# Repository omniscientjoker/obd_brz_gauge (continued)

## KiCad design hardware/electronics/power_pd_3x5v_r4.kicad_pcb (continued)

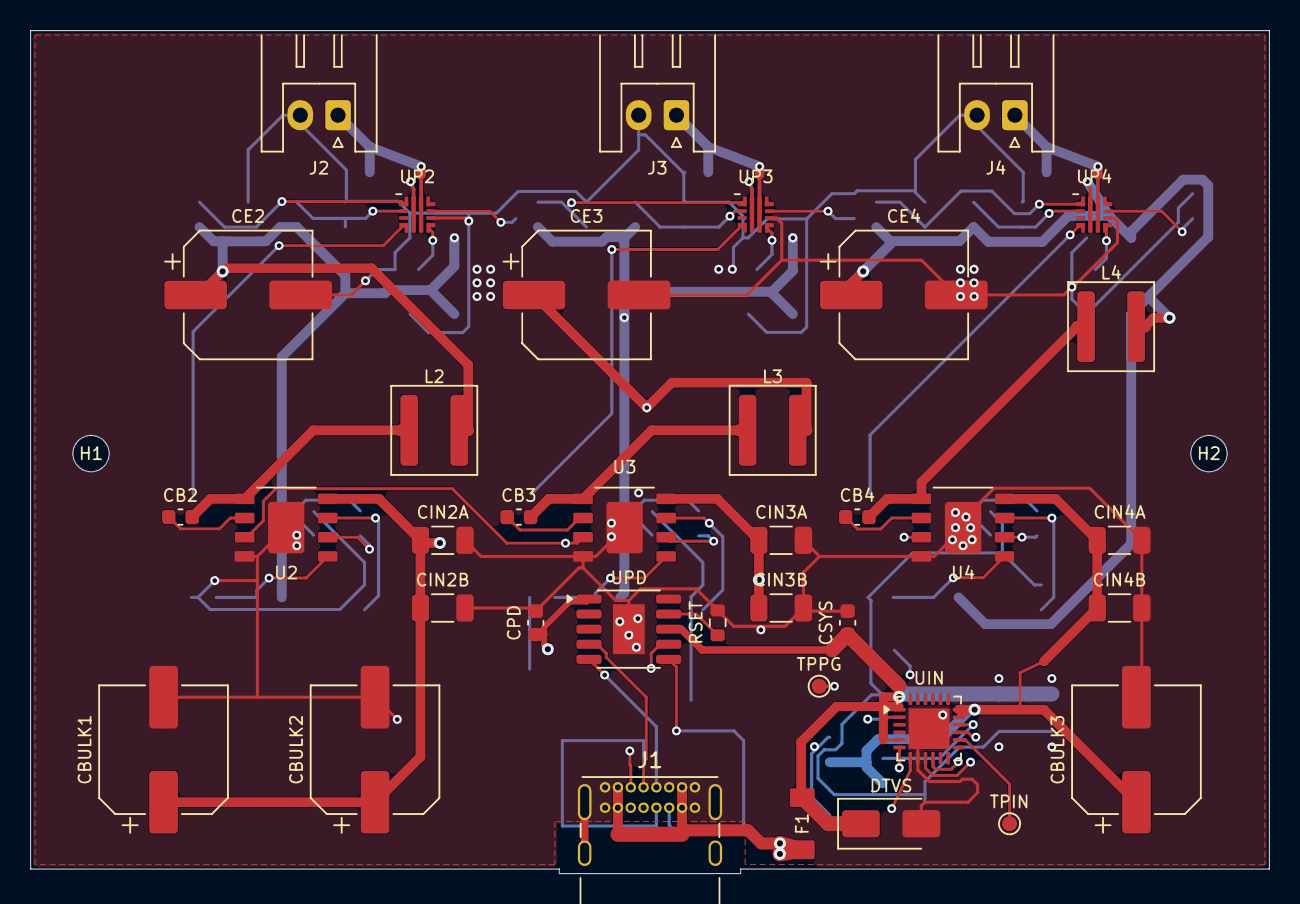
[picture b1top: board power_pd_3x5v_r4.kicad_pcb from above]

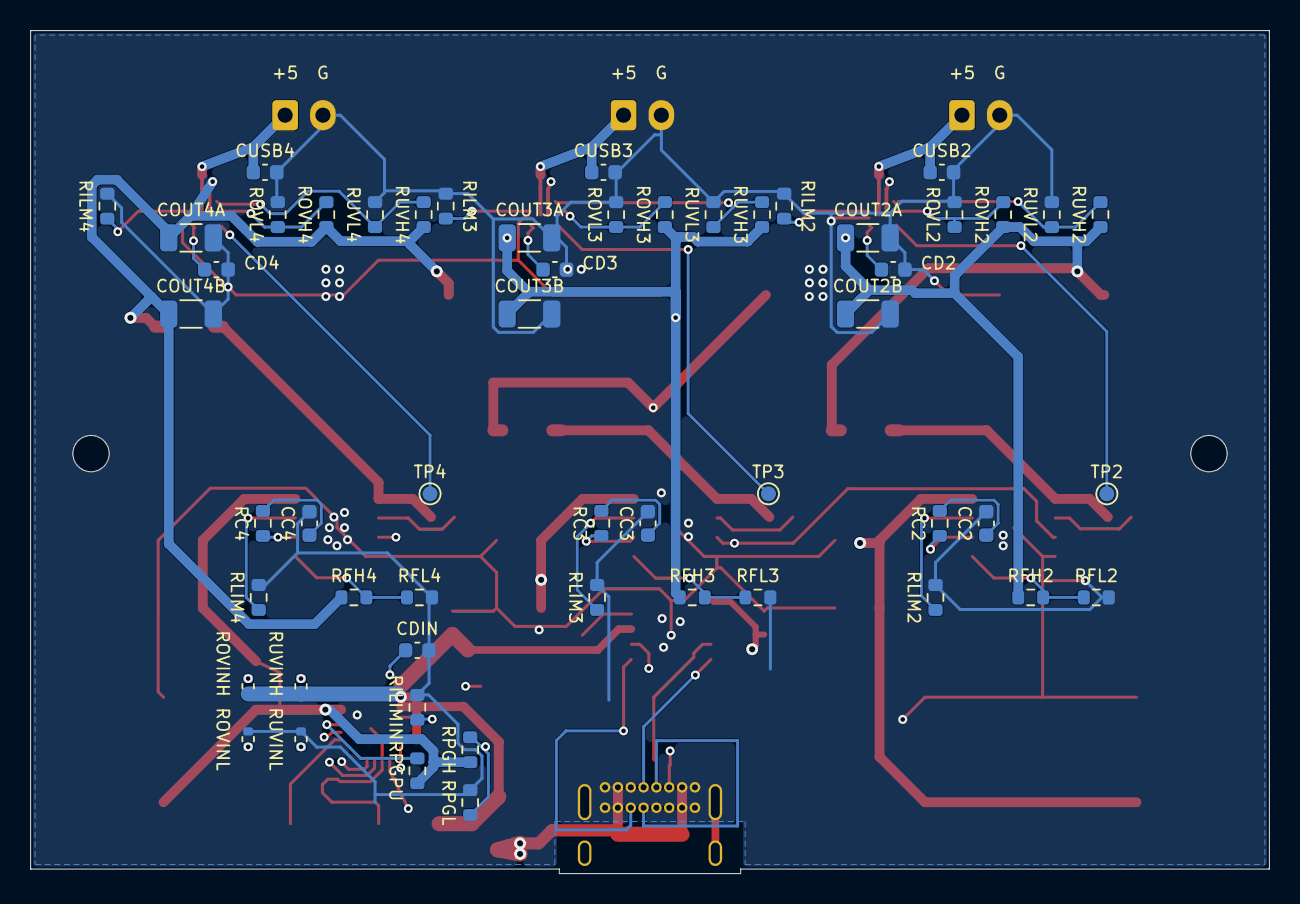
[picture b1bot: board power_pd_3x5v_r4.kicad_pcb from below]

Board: 4 copper layers, 82.0 x 55.8 mm, 93 parts (54 on the bottom side), 55 nets.

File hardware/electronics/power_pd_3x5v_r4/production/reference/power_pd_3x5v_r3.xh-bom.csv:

"Refs","Value","Footprint","Qty","DNP"
"CB2","100nF 50V","Capacitor_SMD:C_0603_1608Metric","1",""
"CB3","100nF 50V","Capacitor_SMD:C_0603_1608Metric","1",""
"CB4","100nF 50V","Capacitor_SMD:C_0603_1608Metric","1",""
"CBULK1","82uF 35V POLYMER","Capacitor_SMD:CP_Elec_8x6.9","1",""
"CBULK2","82uF 35V POLYMER","Capacitor_SMD:CP_Elec_8x6.9","1",""
"CBULK3","82uF 35V POLYMER","Capacitor_SMD:CP_Elec_8x6.9","1",""
"CC2","2.7nF C0G 50V","Capacitor_SMD:C_0603_1608Metric","1",""
"CC3","2.7nF C0G 50V","Capacitor_SMD:C_0603_1608Metric","1",""
"CC4","2.7nF C0G 50V","Capacitor_SMD:C_0603_1608Metric","1",""
"CD2","8.2nF C0G 50V","Capacitor_SMD:C_0603_1608Metric","1",""
"CD3","8.2nF C0G 50V","Capacitor_SMD:C_0603_1608Metric","1",""
"CD4","8.2nF C0G 50V","Capacitor_SMD:C_0603_1608Metric","1",""
"CDIN?","100nF 50V","Capacitor_SMD:C_0603_1608Metric","1",""
"CE2","100uF 25V POLYMER","Capacitor_SMD:CP_Elec_8x6.9","1",""
"CE3","100uF 25V POLYMER","Capacitor_SMD:CP_Elec_8x6.9","1",""
"CE4","100uF 25V POLYMER","Capacitor_SMD:CP_Elec_8x6.9","1",""
"CIN2A?","10uF 50V X5R","Capacitor_SMD:C_1206_3216Metric","1",""
"CIN2B?","10uF 50V X5R","Capacitor_SMD:C_1206_3216Metric","1",""
"CIN3A?","10uF 50V X5R","Capacitor_SMD:C_1206_3216Metric","1",""
"CIN3B?","10uF 50V X5R","Capacitor_SMD:C_1206_3216Metric","1",""
"CIN4A?","10uF 50V X5R","Capacitor_SMD:C_1206_3216Metric","1",""
"CIN4B?","10uF 50V X5R","Capacitor_SMD:C_1206_3216Metric","1",""
"COUT2A?","22uF 25V X5R","Capacitor_SMD:C_1206_3216Metric","1",""
"COUT2B?","22uF 25V X5R","Capacitor_SMD:C_1206_3216Metric","1",""
"COUT3A?","22uF 25V X5R","Capacitor_SMD:C_1206_3216Metric","1",""
"COUT3B?","22uF 25V X5R","Capacitor_SMD:C_1206_3216Metric","1",""
"COUT4A?","22uF 25V X5R","Capacitor_SMD:C_1206_3216Metric","1",""
"COUT4B?","22uF 25V X5R","Capacitor_SMD:C_1206_3216Metric","1",""
"CPD?","1uF 50V X5R","Capacitor_SMD:C_0603_1608Metric","1",""
"CSYS?","1uF 50V X5R","Capacitor_SMD:C_0603_1608Metric","1",""
"CUSB2","1uF 50V X5R","Capacitor_SMD:C_0603_1608Metric","1",""
"CUSB3","1uF 50V X5R","Capacitor_SMD:C_0603_1608Metric","1",""
"CUSB4","1uF 50V X5R","Capacitor_SMD:C_0603_1608Metric","1",""
"DTVS?","SMAJ16A","Diode_SMD:D_SMA","1",""
"F1","3A 63VDC FAST","GaugePower:SF_1206F_Recommended","1",""
"J1","USB-C PD 15V/3A","Connector_USB:USB_C_Receptacle_GCT_USB4085","1",""
"J2","XH2.50-2P 5V OUTPUT","GaugePower:JST_XH_S2B-XH-A_1x02_P2.50mm_Horizontal_Assembly","1",""
"J3","XH2.50-2P 5V OUTPUT","GaugePower:JST_XH_S2B-XH-A_1x02_P2.50mm_Horizontal_Assembly","1",""
"J4","XH2.50-2P 5V OUTPUT","GaugePower:JST_XH_S2B-XH-A_1x02_P2.50mm_Horizontal_Assembly","1",""
"L2","6.8uH / 6A Isat","Inductor_SMD:L_Coilcraft_XAL5050-XXX","1",""
"L3","6.8uH / 6A Isat","Inductor_SMD:L_Coilcraft_XAL5050-XXX","1",""
"L4","6.8uH / 6A Isat","Inductor_SMD:L_Coilcraft_XAL5050-XXX","1",""
"RC2","24k","Resistor_SMD:R_0603_1608Metric","1",""
"RC3","24k","Resistor_SMD:R_0603_1608Metric","1",""
"RC4","24k","Resistor_SMD:R_0603_1608Metric","1",""
"RFH2","52.3k 0.1%","Resistor_SMD:R_0603_1608Metric","1",""
"RFH3","52.3k 0.1%","Resistor_SMD:R_0603_1608Metric","1",""
"RFH4","52.3k 0.1%","Resistor_SMD:R_0603_1608Metric","1",""
"RFL2","10k 0.1%","Resistor_SMD:R_0603_1608Metric","1",""
"RFL3","10k 0.1%","Resistor_SMD:R_0603_1608Metric","1",""
"RFL4","10k 0.1%","Resistor_SMD:R_0603_1608Metric","1",""
"RILIMIN?","8.25k 1%","Resistor_SMD:R_0603_1608Metric","1",""
"RILM2","1.65k 1%","Resistor_SMD:R_0603_1608Metric","1",""
"RILM3","1.65k 1%","Resistor_SMD:R_0603_1608Metric","1",""
"RILM4","1.65k 1%","Resistor_SMD:R_0603_1608Metric","1",""
"RLIM2","84.5k 1%","Resistor_SMD:R_0603_1608Metric","1",""
"RLIM3","84.5k 1%","Resistor_SMD:R_0603_1608Metric","1",""
"RLIM4","84.5k 1%","Resistor_SMD:R_0603_1608Metric","1",""
"ROVH2","34k 0.1%","Resistor_SMD:R_0603_1608Metric","1",""
"ROVH3","34k 0.1%","Resistor_SMD:R_0603_1608Metric","1",""
"ROVH4","34k 0.1%","Resistor_SMD:R_0603_1608Metric","1",""
"ROVINH?","133k 0.1%","Resistor_SMD:R_0402_1005Metric","1",""
"ROVINL?","10k 0.1%","Resistor_SMD:R_0402_1005Metric","1",""
"ROVL2","10k 0.1%","Resistor_SMD:R_0603_1608Metric","1",""
"ROVL3","10k 0.1%","Resistor_SMD:R_0603_1608Metric","1",""
"ROVL4","10k 0.1%","Resistor_SMD:R_0603_1608Metric","1",""
"RPGH?","100k 0.1%","Resistor_SMD:R_0603_1608Metric","1",""
"RPGL?","10k 0.1%","Resistor_SMD:R_0603_1608Metric","1",""
"RPGPU?","100k","Resistor_SMD:R_0603_1608Metric","1",""
"RSET?","56k 1%","Resistor_SMD:R_0603_1608Metric","1",""
"RUVH2","28k 0.1%","Resistor_SMD:R_0603_1608Metric","1",""
"RUVH3","28k 0.1%","Resistor_SMD:R_0603_1608Metric","1",""
"RUVH4","28k 0.1%","Resistor_SMD:R_0603_1608Metric","1",""
"RUVINH?","100k 0.1%","Resistor_SMD:R_0402_1005Metric","1",""
"RUVINL?","10k 0.1%","Resistor_SMD:R_0402_1005Metric","1",""
"RUVL2","10k 0.1%","Resistor_SMD:R_0603_1608Metric","1",""
"RUVL3","10k 0.1%","Resistor_SMD:R_0603_1608Metric","1",""
"RUVL4","10k 0.1%","Resistor_SMD:R_0603_1608Metric","1",""
"U2","RT7272BGSP","GaugePower:RT7272BGSP_PSOP8_Option2","1",""
"U3","RT7272BGSP","GaugePower:RT7272BGSP_PSOP8_Option2","1",""
"U4","RT7272BGSP","GaugePower:RT7272BGSP_PSOP8_Option2","1",""
"UIN?","TPS26630RGER","GaugePower:Texas_RGE0024H_VQFN-24-1EP_4x4mm_P0.5mm_EP2.7x2.7mm_Assembly","1",""
"UP2","TPS259470LRPWR","GaugePower:TI_RPW0010A","1",""
"UP3","TPS259470LRPWR","GaugePower:TI_RPW0010A","1",""
"UP4","TPS259470LRPWR","GaugePower:TI_RPW0010A","1",""
"UPD?","CH224A","Package_SO:SSOP-10-1EP_3.9x4.9mm_P1mm_EP2.1x3.3mm","1",""
